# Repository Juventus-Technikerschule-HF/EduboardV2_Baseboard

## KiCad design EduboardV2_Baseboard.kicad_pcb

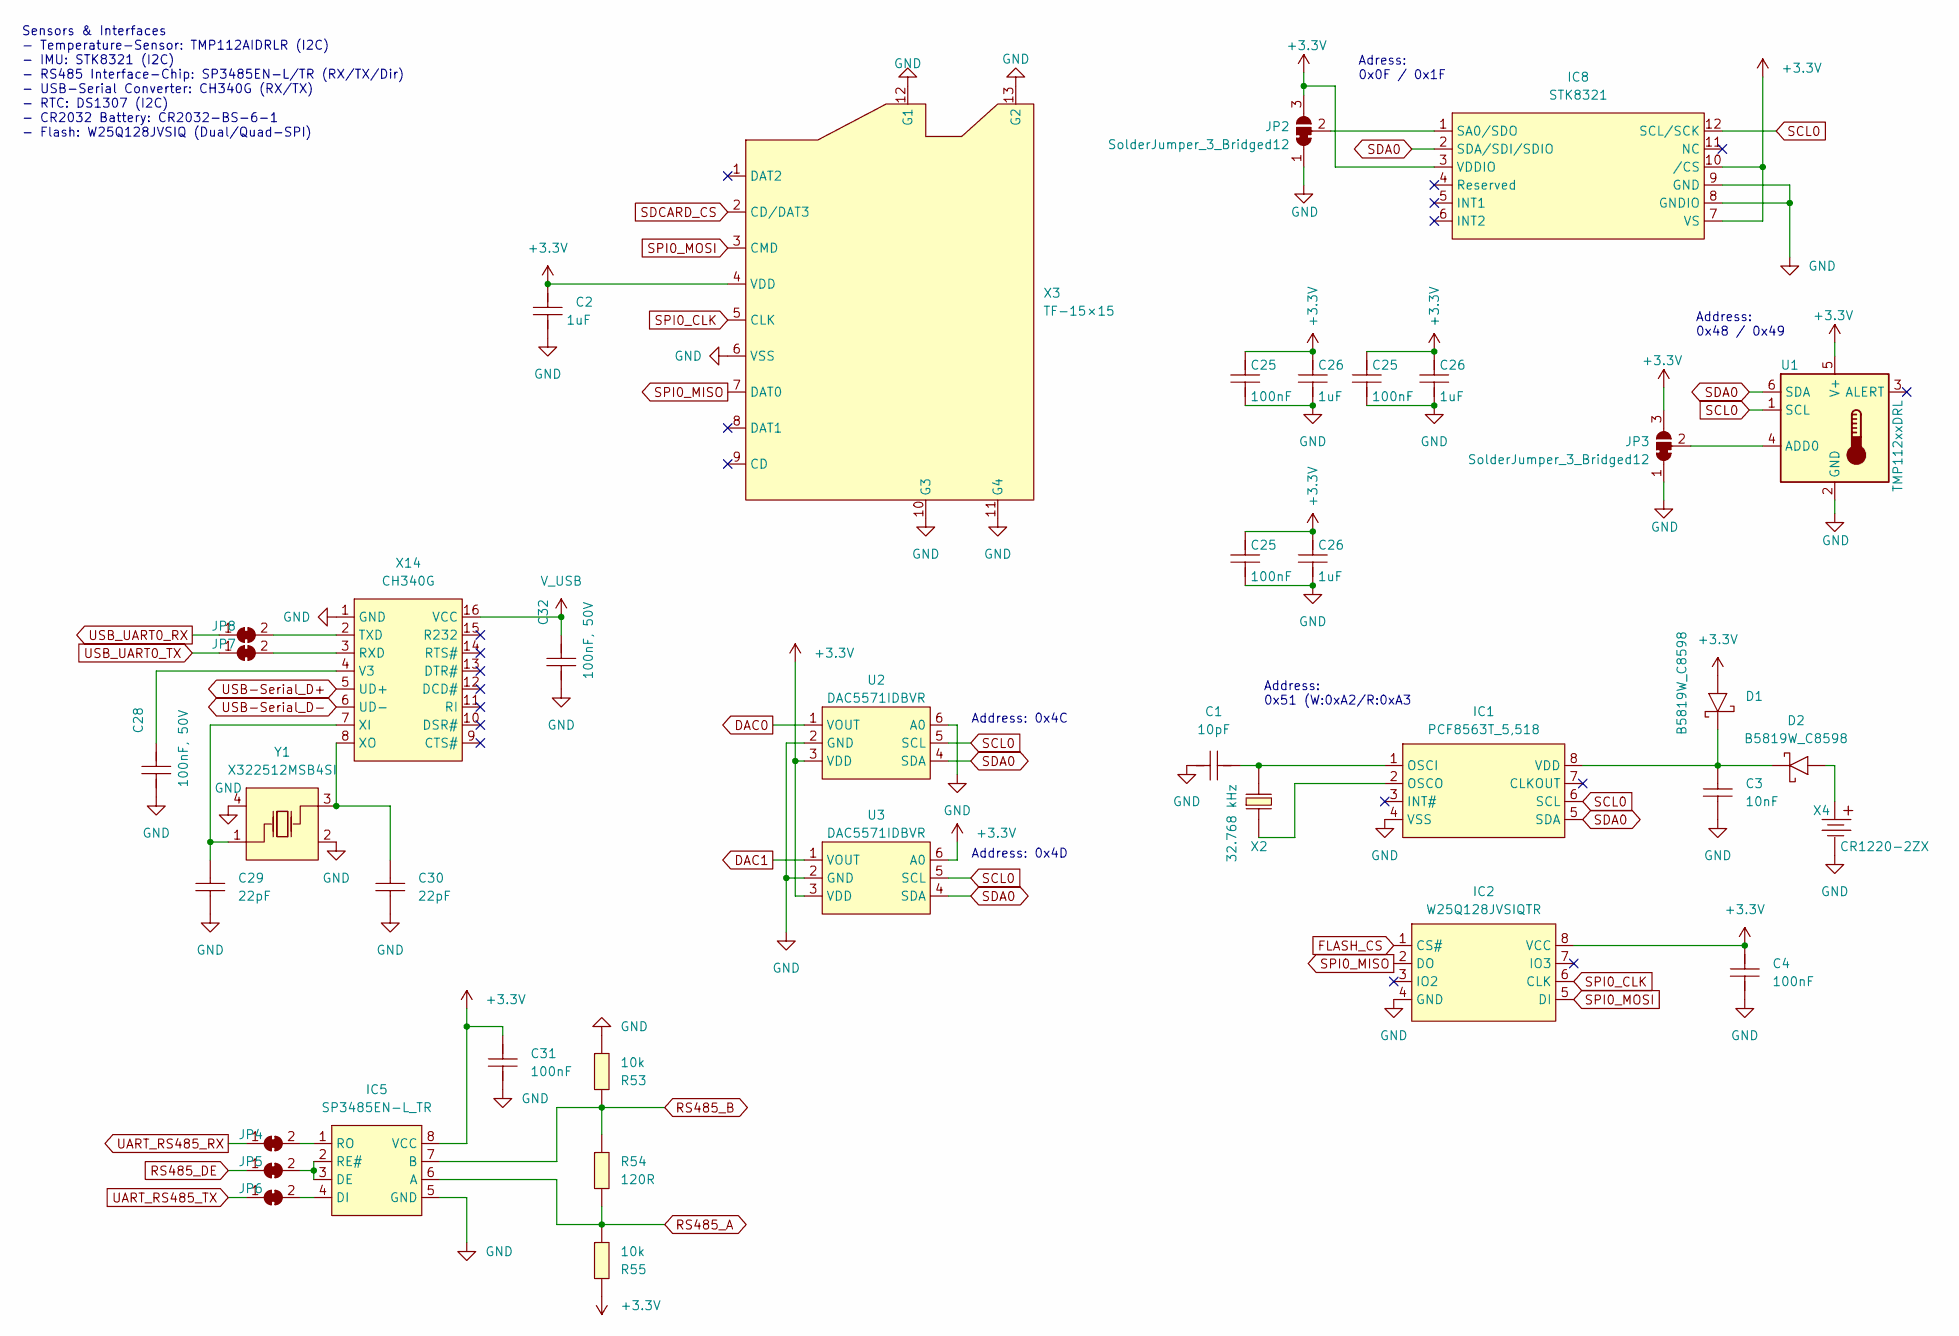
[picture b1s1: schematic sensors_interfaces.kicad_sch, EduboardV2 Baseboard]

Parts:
C1: 10pF; C_0402_1005Metric_Pad0.74x0.62mm_HandSolder; MPN CL05C100JB5NNNC; LCSC Part C32949
C2, C26: 1uF; C_0402_1005Metric_Pad0.74x0.62mm_HandSolder; MPN CL05A105KA5NQNC; LCSC Part C52923
C3: 10nF; C_0402_1005Metric_Pad0.74x0.62mm_HandSolder; MPN CL05B103KB5NNNC; LCSC Part C15195
C4, C25, C31: 100nF; C_0402_1005Metric_Pad0.74x0.62mm_HandSolder; MPN CL05B104KB54PNC; LCSC Part C307331
C28, C32: 100nF, 50V; C_0402_1005Metric_Pad0.74x0.62mm_HandSolder; MPN CL05B104KB54PNC; LCSC Part C307331
C29, C30: 22pF; C_0402_1005Metric_Pad0.74x0.62mm_HandSolder; MPN 0402CG220J500NT; LCSC Part C1555
D1, D2: B5819W_C8598; SOD-123_L2.7-W1.6-LS3.7-RD-1; MPN B5819W_C8598; LCSC Part C8598
IC1: PCF8563T_5,518; SOIC-8_L5.0-W4.0-P1.27-LS6.0-BL; MPN PCF8563T/5,518; LCSC Part C7440
IC2: W25Q128JVSIQTR; SOIC-8_L5.3-W5.3-P1.27-LS8.0-BL; MPN W25Q128JVSIQTR; LCSC Part C97521
IC5: SP3485EN-L_TR; SOIC-8_L5.0-W4.0-P1.27-LS6.0-BL; MPN SP3485EN-L/TR; LCSC Part C8963
IC8: STK8321; LGA-12_L2.0-W2.0-P0.50-TR; MPN STK8321; LCSC Part C966924
JP2, JP3: SolderJumper_3_Bridged12; SolderJumper-3_P1.3mm_Bridged12_Pad1.0x1.5mm
JP4, JP5, JP6, JP7, JP8: SolderJumper_2_Bridged; SolderJumper-2_P1.3mm_Bridged_Pad1.0x1.5mm
R53, R55: 10k; R_0402_1005Metric_Pad0.72x0.64mm_HandSolder; MPN 0402WGF1002TCE; LCSC Part C25744
R54: 120R; R_0402_1005Metric_Pad0.72x0.64mm_HandSolder; MPN 0402WGF1200TCE; LCSC Part C25079
U1: TMP112xxDRL; SOT-563; LCSC Part C28927
U2, U3: DAC5571IDBVR; SOT-23-6_L2.9-W1.6-P0.95-LS2.8-BR; LCSC Part C24061
X2: 32.768 kHz; FC-135R_L3.2-W1.5; MPN Q13FC1350000400; LCSC Part C32346
X3: TF-15×15; TF-SMD_TF-15-15; MPN TF-15×15; LCSC Part C111196
X4: CR1220-2ZX; BAT-SMD_CR1220-2ZX; MPN CR1220-2ZX; LCSC Part C969906
X14: CH340G; SOIC-16_L9.9-W3.9-P1.27-LS6.0-BL; MPN CH340G; LCSC Part C14267
Y1: X322512MSB4SI; OSC-SMD_4P-L3.2-W2.5-BL; MPN X322512MSB4SI; LCSC Part C9002

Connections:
FLASH_CS: IC2.1 (CS#); also elsewhere on the board
unnamed: C3.2, D1.1 (-), D2.1 (-), IC1.8 (VDD)
unnamed: IC5.2 (RE#), IC5.3 (DE), JP5.2 (B)
unnamed: IC5.4 (DI), JP6.2 (B)
unnamed: IC5.1 (RO), JP4.2 (B)
unnamed: IC8.1 (SA0/SDO), JP2.2 (C)
unnamed: JP3.2 (C), U1.4 (ADD0)
unnamed: JP7.2 (B), X14.3 (RXD)
unnamed: JP8.2 (B), X14.2 (TXD)
unnamed: C28.2, X14.4 (V3)
unnamed: C29.2, X14.7 (XI), Y1.1 (OSC1)
unnamed: C30.2, X14.8 (XO), Y1.3 (OSC2)
RS485_A: IC5.6 (A), R54.1, R55.1; also elsewhere on the board
RS485_B: IC5.7 (B), R53.2, R54.2; also elsewhere on the board
RS485_DE: JP5.1 (A); also elsewhere on the board
SCL0: IC1.6 (SCL), IC8.12 (SCL/SCK), U1.1 (SCL), U2.5 (SCL), U3.5 (SCL); also elsewhere on the board
SDA0: IC1.5 (SDA), IC8.2 (SDA/SDI/SDIO), U1.6 (SDA), U2.4 (SDA), U3.4 (SDA); also elsewhere on the board
SDCARD_CS: X3.2 (CD/DAT3); also elsewhere on the board
SPI0_MISO: IC2.2 (DO), X3.7 (DAT0); also elsewhere on the board
SPI0_MOSI: IC2.5 (DI), X3.3 (CMD); also elsewhere on the board
UART_RS485_RX: JP4.1 (A); also elsewhere on the board
UART_RS485_TX: JP6.1 (A); also elsewhere on the board
USB-Serial_D+: X14.5 (UD+); also elsewhere on the board
USB-Serial_D-: X14.6 (UD-); also elsewhere on the board
USB_UART0_TX: JP7.1 (A); also elsewhere on the board
V_USB: C32.2, X14.16 (VCC); also elsewhere on the board

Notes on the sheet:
Sensors & Interfaces - Temperature-Sensor: TMP112AIDRLR (I2C) - IMU: STK8321 (I2C) - RS485 Interface-Chip: SP3485EN-L/TR (RX/TX/Dir) - USB-Serial Converter: CH340G (RX/TX) - RTC: DS1307 (I2C) - CR2032 Battery: CR2032-BS-6-1 - Flash: W25Q128JVSIQ (Dual/Quad-SPI)
Adress: 0x0F / 0x1F
Address: 0x51 (W:0xA2/R:0xA3
Address: 0x4C
Address: 0x48 / 0x49
Address: 0x4D

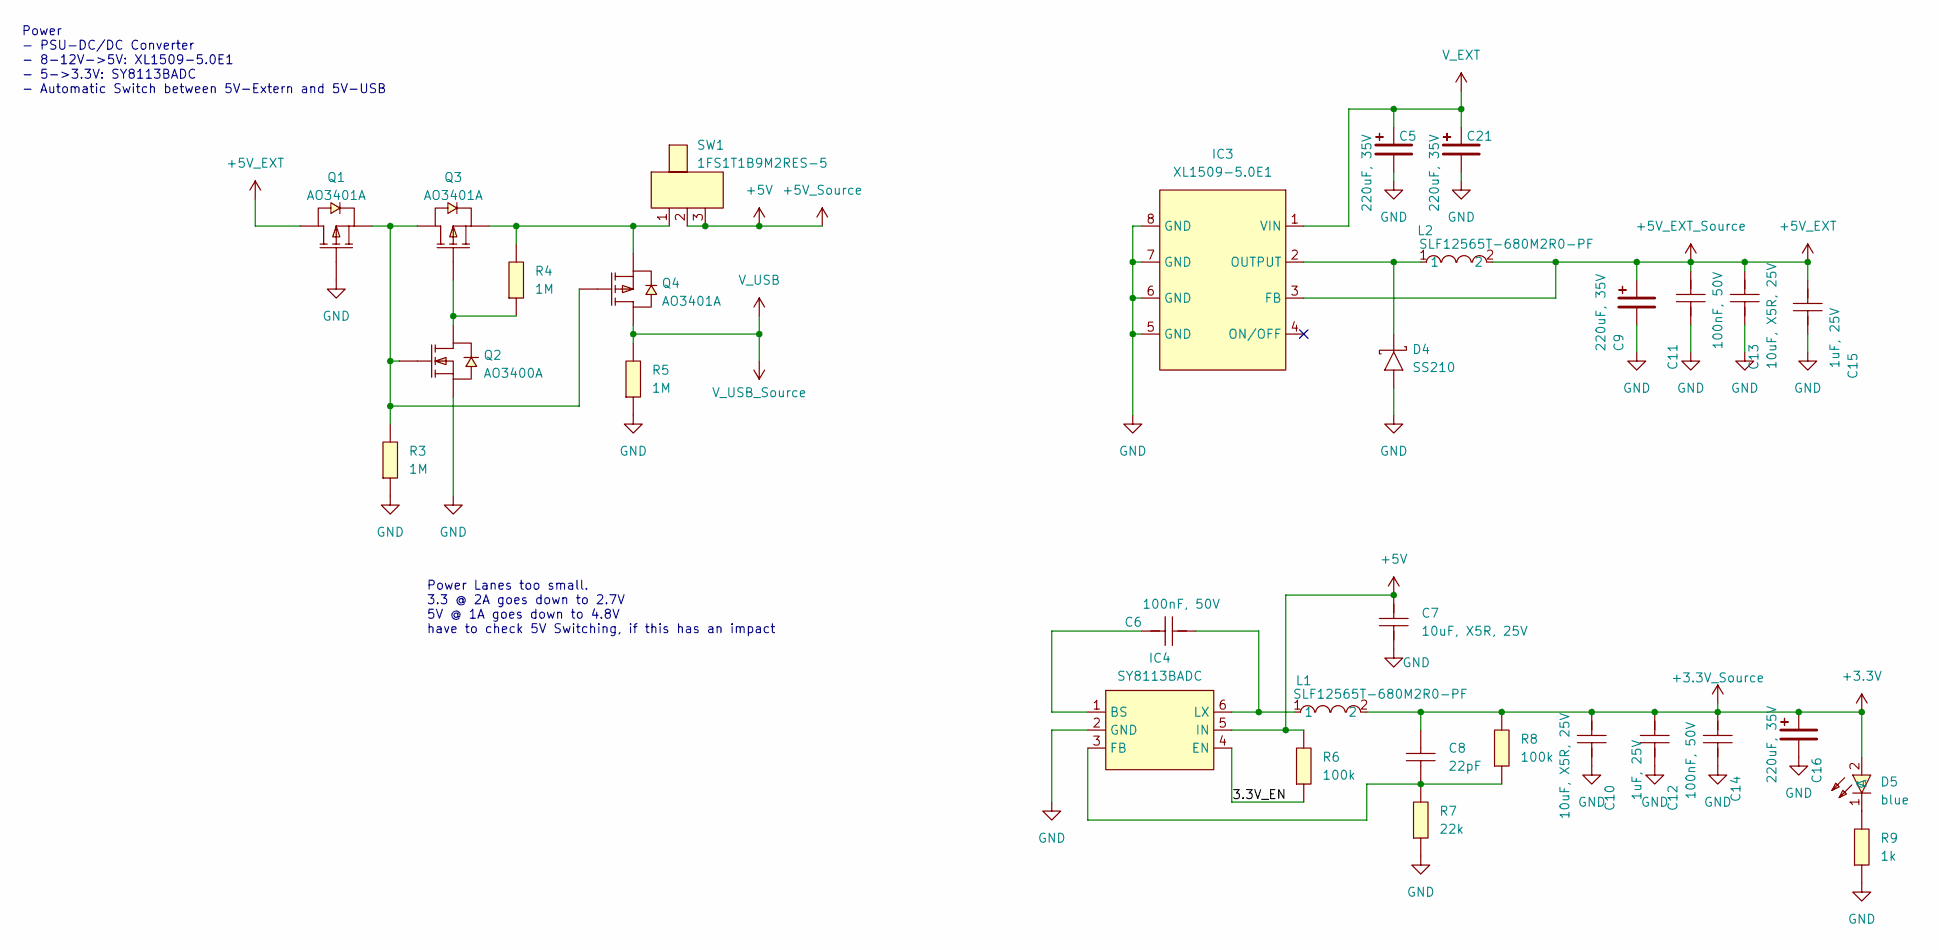
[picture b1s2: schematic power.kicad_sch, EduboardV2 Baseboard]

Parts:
C5, C9, C16, C21: 220uF, 35V; CAP-SMD_BD8.0-L8.3-W8.3-RD; MPN VEJ221M1VTR-0810; LCSC Part C164065
C6, C11, C14: 100nF, 50V; C_0402_1005Metric_Pad0.74x0.62mm_HandSolder; MPN CL05B104KB54PNC; LCSC Part C307331
C7, C10, C13: 10uF, X5R, 25V; C_0603_1608Metric_Pad1.08x0.95mm_HandSolder; MPN CL10A106MA8NRNC; LCSC Part C96446
C8: 22pF; C_0402_1005Metric_Pad0.74x0.62mm_HandSolder; MPN 0402CG220J500NT; LCSC Part C1555
C12, C15: 1uF, 25V; C_0402_1005Metric_Pad0.74x0.62mm_HandSolder; MPN CL05A105KA5NQNC; LCSC Part C52923
D4: SS210; SMA_L4.3-W2.6-LS5.2-RD; MPN SS210; LCSC Part C14996
D5: blue; LED0603-FD_BLUE; MPN 19-217/BHC-ZL1M2RY/3T; LCSC Part C72041
IC3: XL1509-5.0E1; SOIC-8_L5.0-W4.0-P1.27-LS6.0-BL; MPN XL1509-5.0E1; LCSC Part C61063
IC4: SY8113BADC; TSOT-23-6_L2.9-W1.6-P0.95-LS2.8-BR; MPN SY8113BADC; LCSC Part C78989
L1, L2: SLF12565T-680M2R0-PF; IND-SMD_L12.5-W12.5_SLF12565T; LCSC Part C136216
Q1, Q3, Q4: AO3401A; SOT-23_L2.9-W1.3-P1.90-LS2.4-BR; MPN AO3401A; LCSC Part C15127
Q2: AO3400A; SOT-23-3_L2.9-W1.6-P1.90-LS2.8-BR; MPN AO3400A; LCSC Part C20917
R3, R4, R5: 1M; R_0402_1005Metric_Pad0.72x0.64mm_HandSolder; MPN 0402WGF1003TCE; LCSC Part C25741
R6, R8: 100k; R_0402_1005Metric_Pad0.72x0.64mm_HandSolder; MPN 0402WGF1003TCE; LCSC Part C25741
R7: 22k; R_0402_1005Metric_Pad0.72x0.64mm_HandSolder; MPN 0402WGF2202TCE; LCSC Part C25768
R9: 1k; R_0402_1005Metric_Pad0.72x0.64mm_HandSolder; MPN 0402WGF1001TCE; LCSC Part C11702
SW1: 1FS1T1B9M2RES-5; SW-TH_1FS1T1B9M2RES-5; MPN 1FS1T1B9M2RES-5; LCSC Part C496164

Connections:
+5V: C7.2, IC4.5 (IN), R6.2, SW1.2, SW1.3; also elsewhere on the board
+5V_EXT: C9.1, C11.1, C13.2, C15.1, IC3.3 (FB), L2.2, Q1.3 (D)
/Power/3.3V_EN: IC4.4 (EN), R6.1
unnamed: D4.1 (K), IC3.2 (OUTPUT), L2.1
unnamed: D5.1 (C), R9.2
unnamed: C6.1, IC4.1 (BS)
unnamed: C8.1, IC4.3 (FB), R7.2, R8.1
unnamed: C6.2, IC4.6 (LX), L1.1
unnamed: Q1.2 (S), Q2.1 (G), Q3.3 (D), Q4.1 (G), R3.2
unnamed: Q2.3 (D), Q3.1 (G), R4.1
unnamed: Q3.2 (S), Q4.2 (S), R4.2, SW1.1
V_USB: Q4.3 (D), R5.2; also elsewhere on the board

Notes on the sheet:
Power Lanes too small. 3.3 @ 2A goes down to 2.7V 5V @ 1A goes down to 4.8V have to check 5V Switching, if this has an impact
Power - PSU-DC/DC Converter - 8-12V->5V: XL1509-5.0E1 - 5->3.3V: SY8113BADC - Automatic Switch between 5V-Extern and 5V-USB

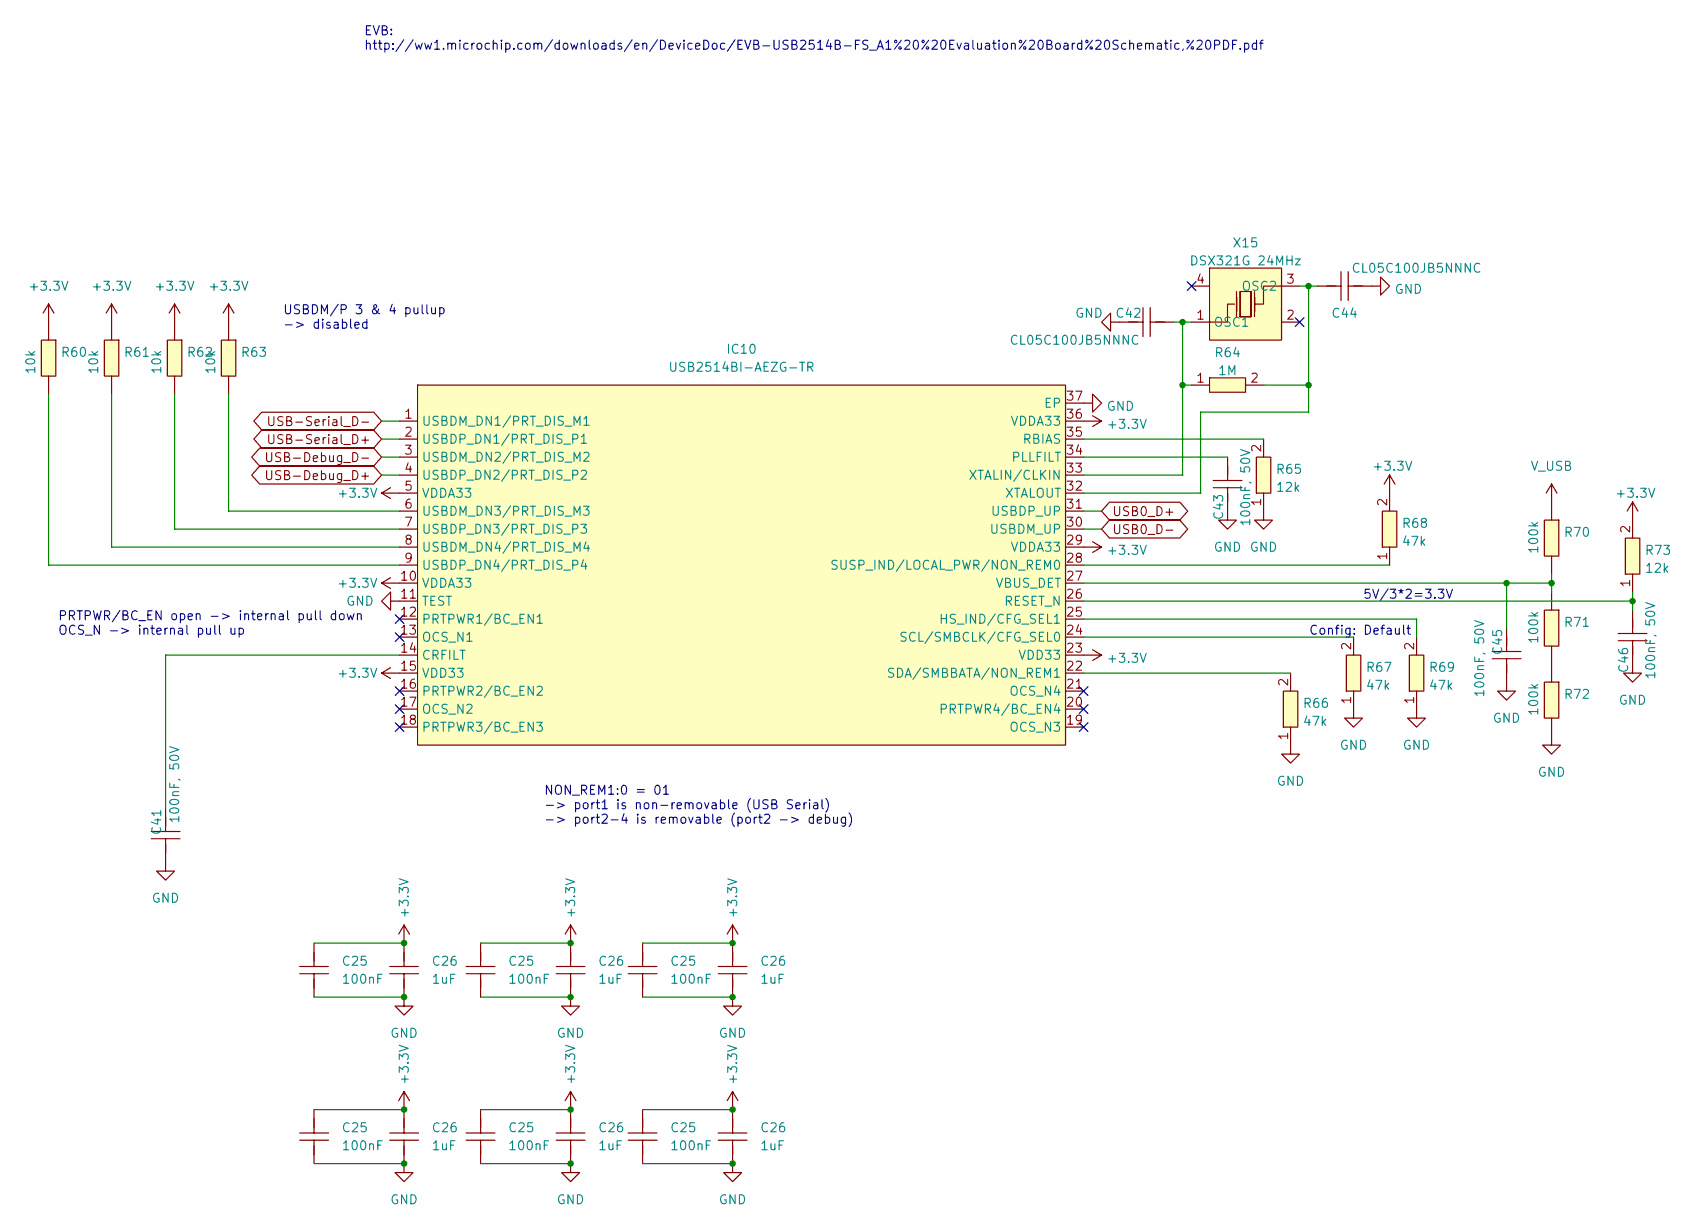
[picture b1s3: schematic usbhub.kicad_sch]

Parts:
C25: 100nF; C_0402_1005Metric_Pad0.74x0.62mm_HandSolder; MPN CL05B104KB54PNC; LCSC Part C307331
C26: 1uF; C_0402_1005Metric_Pad0.74x0.62mm_HandSolder; MPN CL05A105KA5NQNC; LCSC Part C52923
C41, C43, C45, C46: 100nF, 50V; C_0402_1005Metric_Pad0.74x0.62mm_HandSolder; MPN CL05B104KB54PNC; LCSC Part C307331
C42, C44: CL05C100JB5NNNC; C_0402_1005Metric_Pad0.74x0.62mm_HandSolder; MPN CL05C100JB5NNNC; LCSC Part C32949
IC10: USB2514BI-AEZG-TR; TQFN-36_L6.0-W6.0-P0.50-BL-EP3.7; MPN USB2514BI-AEZG-TR; LCSC Part C58940
R60, R61, R62, R63: 10k; R_0402_1005Metric_Pad0.72x0.64mm_HandSolder; MPN 0402WGF1002TCE; LCSC Part C25744
R64: 1M; R_0402_1005Metric_Pad0.72x0.64mm_HandSolder; LCSC Part C25741
R65, R73: 12k; R_0402_1005Metric_Pad0.72x0.64mm_HandSolder; LCSC Part C25752
R66, R67, R68, R69: 47k; R_0402_1005Metric_Pad0.72x0.64mm_HandSolder; LCSC Part C25792
R70, R71, R72: 100k; R_0402_1005Metric_Pad0.72x0.64mm_HandSolder; MPN 0402WGF1003TCE; LCSC Part C25741
X15: DSX321G 24MHz; OSC-SMD_4P-L3.2-W2.5-BL; LCSC Part C93235

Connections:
unnamed: C41.1, IC10.14 (CRFILT)
unnamed: IC10.25 (HS_IND/CFG_SEL1), R69.2
unnamed: C43.1, IC10.34 (PLLFILT)
unnamed: IC10.35 (RBIAS), R65.2
unnamed: C46.1, IC10.26 (RESET_N), R73.1
unnamed: IC10.24 (SCL/SMBCLK/CFG_SEL0), R67.2
unnamed: IC10.22 (SDA/SMBBATA/NON_REM1), R66.2
unnamed: IC10.28 (SUSP_IND/LOCAL_PWR/NON_REM0), R68.1
unnamed: IC10.6 (USBDM_DN3/PRT_DIS_M3), R63.2
unnamed: IC10.8 (USBDM_DN4/PRT_DIS_M4), R61.2
unnamed: IC10.7 (USBDP_DN3/PRT_DIS_P3), R62.2
unnamed: IC10.9 (USBDP_DN4/PRT_DIS_P4), R60.2
unnamed: C45.1, IC10.27 (VBUS_DET), R70.2, R71.1
unnamed: C42.2, IC10.33 (XTALIN/CLKIN), R64.1, X15.1 (OSC1)
unnamed: C44.1, IC10.32 (XTALOUT), R64.2, X15.3 (OSC2)
unnamed: R71.2, R72.1
USB0_D+: IC10.31 (USBDP_UP); also elsewhere on the board
USB0_D-: IC10.30 (USBDM_UP); also elsewhere on the board
USB-Debug_D+: IC10.4 (USBDP_DN2/PRT_DIS_P2); also elsewhere on the board
USB-Debug_D-: IC10.3 (USBDM_DN2/PRT_DIS_M2); also elsewhere on the board
USB-Serial_D+: IC10.2 (USBDP_DN1/PRT_DIS_P1); also elsewhere on the board
USB-Serial_D-: IC10.1 (USBDM_DN1/PRT_DIS_M1); also elsewhere on the board
V_USB: R70.1; also elsewhere on the board

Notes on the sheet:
PRTPWR/BC_EN open -> internal pull down OCS_N -> internal pull up
EVB: http://ww1.microchip.com/downloads/en/DeviceDoc/EVB-USB2514B-FS_A1%20%20Evaluation%20Board%20Schematic,%20PDF.pdf
5V/3*2=3.3V
Config: Default
USBDM/P 3 & 4 pullup -> disabled
NON_REM1:0 = 01 -> port1 is non-removable (USB Serial) -> port2-4 is removable (port2 -> debug)

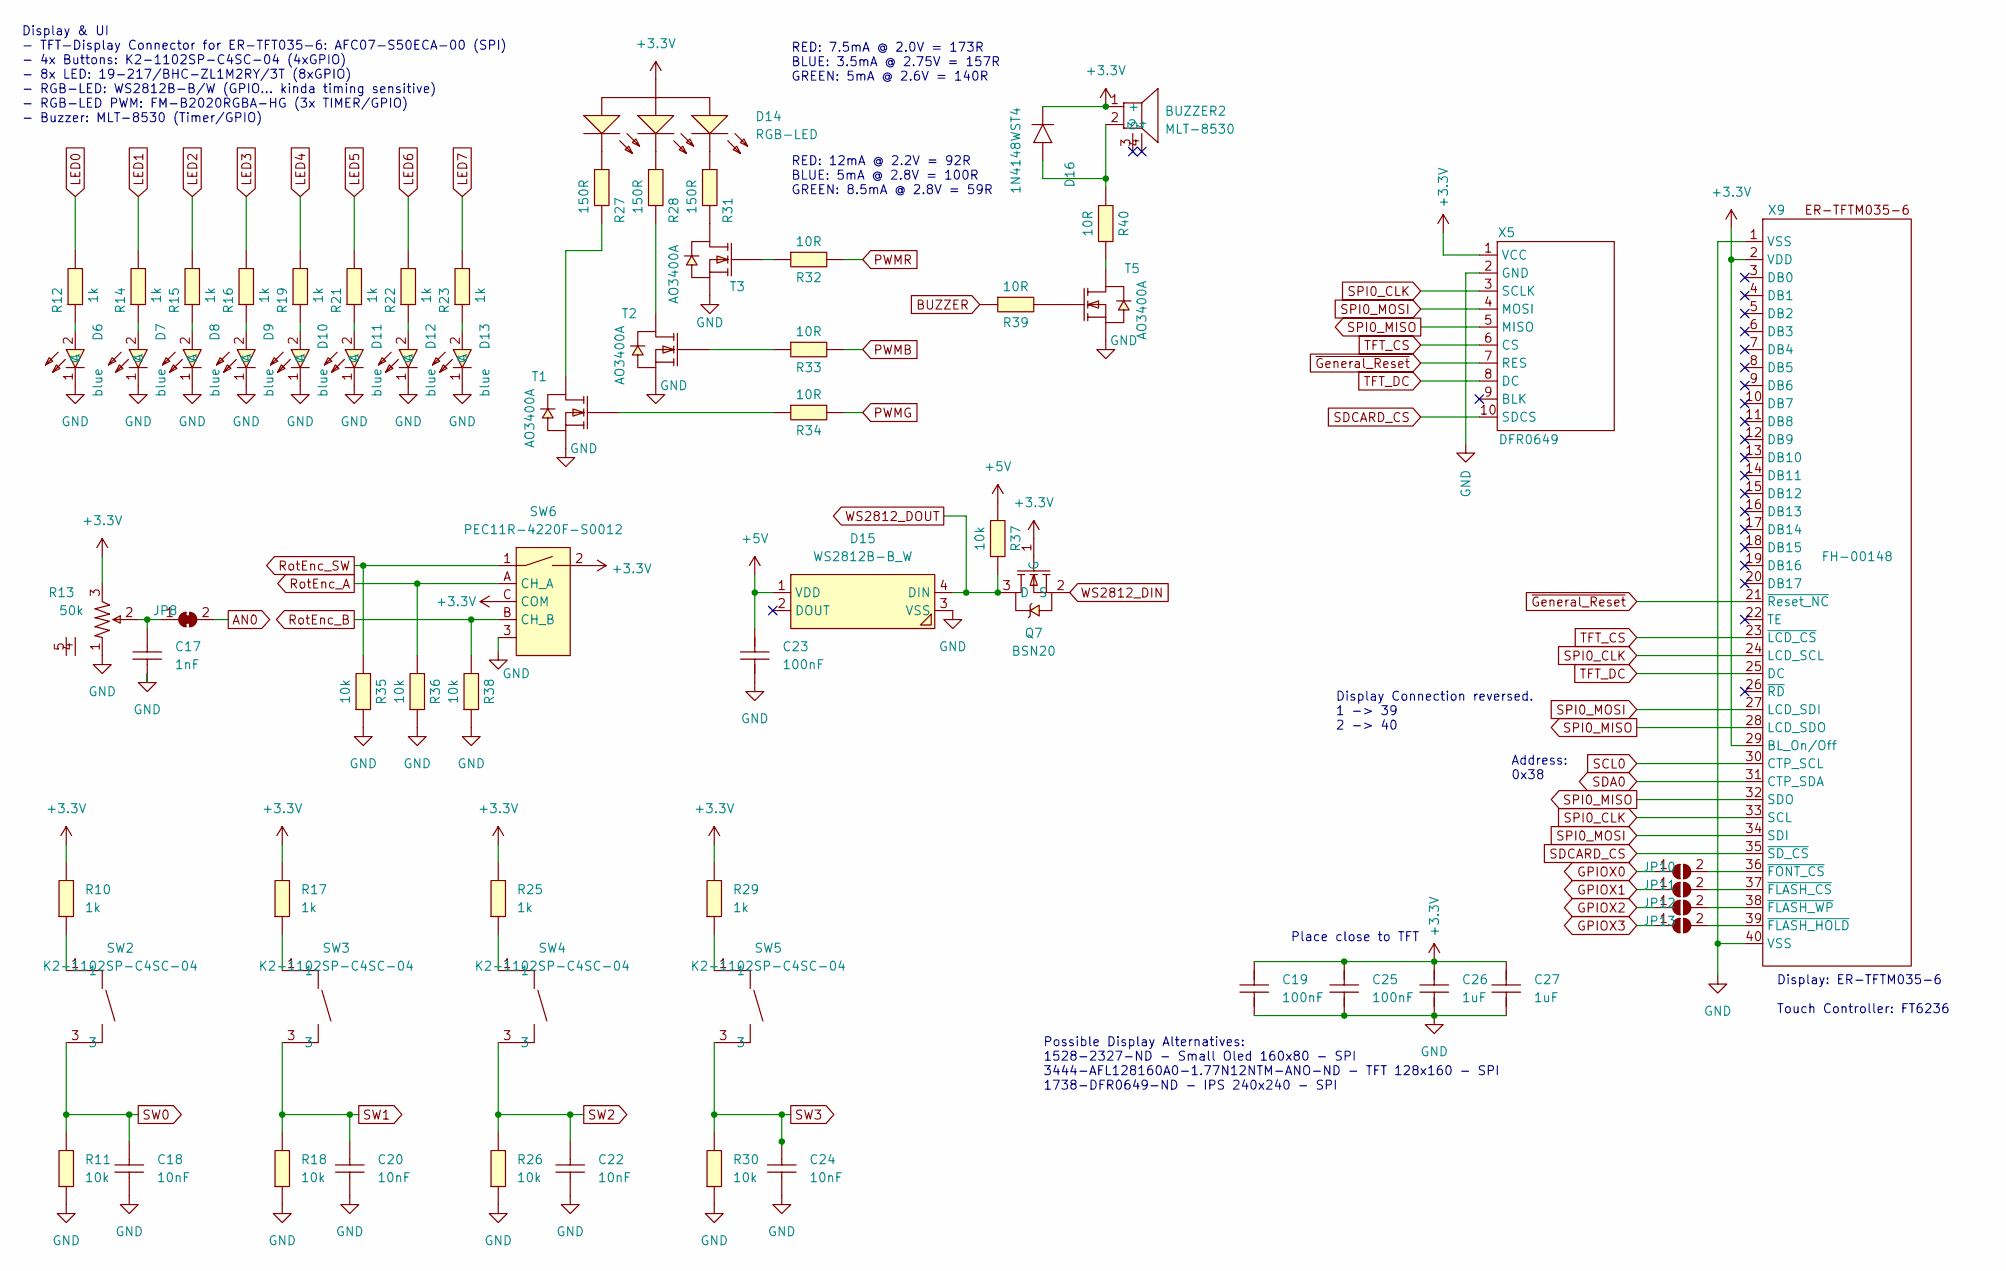
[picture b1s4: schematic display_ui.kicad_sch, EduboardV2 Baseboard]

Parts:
BUZZER2: MLT-8530; BUZ-SMD_4P-L8.5-W8.5-P8.50-BR; LCSC Part C94599
C17: 1nF; C_0402_1005Metric_Pad0.74x0.62mm_HandSolder; MPN 0402B102K500NT; LCSC Part C1523
C18, C20, C22, C24: 10nF; C_0402_1005Metric_Pad0.74x0.62mm_HandSolder; MPN CL05B103KB5NNNC; LCSC Part C15195
C19, C23, C25: 100nF; C_0402_1005Metric_Pad0.74x0.62mm_HandSolder; MPN CL05B104KB54PNC; LCSC Part C307331
C26, C27: 1uF; C_0402_1005Metric_Pad0.74x0.62mm_HandSolder; MPN CL05A105KA5NQNC; LCSC Part C52923
D6, D7, D8, D9, D10, D11, D12, D13: blue; LED0603-FD_BLUE; MPN 19-217/BHC-ZL1M2RY/3T; LCSC Part C72041
D14: RGB-LED; LED-SMD_FM-B2020RGBA-HG; MPN FM-B2020RGBA-HG; LCSC Part C108793
D15: WS2812B-B_W; LED-SMD_4P-L5.0-W5.0-TL_WS2812B-B; MPN WS2812B-B/W; LCSC Part C2761795
D16: 1N4148WST4; SOD-323_L1.8-W1.3-LS2.5-RD; MPN 1N4148WS T4; LCSC Part C2128
JP8: SolderJumper_2_Bridged; SolderJumper-2_P1.3mm_Bridged_Pad1.0x1.5mm
JP10, JP11, JP12, JP13: SolderJumper_2_Open; SolderJumper-2_P1.3mm_Open_Pad1.0x1.5mm
Q7: BSN20; SOT-23-3_L2.9-W1.6-P1.90-LS2.8-BR; LCSC Part C116157
R10, R12, R14, R15, R16, R17, R19, R21, R22, R23, R25, R29: 1k; R_0402_1005Metric_Pad0.72x0.64mm_HandSolder; MPN 0402WGF1001TCE; LCSC Part C11702
R11, R18, R26, R30: 10k; R_0402_1005Metric_Pad0.72x0.64mm_HandSolder; MPN 0402WGF1002TCE; LCSC Part C25744
R13: 50k; RES-TH_RK09K1130AAU; MPN RK09K1130ACL; LCSC Part C470291
R27, R28, R31: 150R; R_0402_1005Metric_Pad0.72x0.64mm_HandSolder; MPN 0402WGF1500TCE; LCSC Part C25082
R32, R33, R34, R39, R40: 10R; R_0402_1005Metric_Pad0.72x0.64mm_HandSolder; MPN 0402WGF100JTCE; LCSC Part C25077
R35, R36, R37, R38: 10k; R_0402_1005Metric_Pad0.72x0.64mm_HandSolder; MPN 0402WGF100JTCE; LCSC Part C25744
SW2, SW3, SW4, SW5: K2-1102SP-C4SC-04; KEY-SMD_4P-L6.0-W6.0-P4.50-LS9.5-BL; LCSC Part C127509
SW6: PEC11R-4220F-S0012; SW-TH_PEC11R-4220F-S0012; MPN PEC11R-4220F-S0012; LCSC Part C143817
T1, T2, T3, T5: AO3400A; SOT-23-3_L2.9-W1.6-P1.90-LS2.8-BR; MPN AO3400A; LCSC Part C20917
X5: DFR0649; Digikey 1738-DFR0649-ND
X9: FH-00148; HDR-SMD_40P-P2.54-V-F-R2-C20-S7.1-EH; MPN FH-00148; LCSC Part C2685092

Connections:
+5V: C23.2, D15.1 (VDD), R37.2; also elsewhere on the board
BUZZER: R39.1; also elsewhere on the board
GPIOX0: JP10.1 (A); also elsewhere on the board
GPIOX1: JP11.1 (A); also elsewhere on the board
GPIOX2: JP12.1 (A); also elsewhere on the board
GPIOX3: JP13.1 (A); also elsewhere on the board
LED0: R12.2; also elsewhere on the board
LED1: R14.2; also elsewhere on the board
LED2: R15.2; also elsewhere on the board
LED3: R16.2; also elsewhere on the board
LED4: R19.2; also elsewhere on the board
LED5: R21.2; also elsewhere on the board
LED6: R22.2; also elsewhere on the board
LED7: R23.2; also elsewhere on the board
unnamed: D6.2 (A), R12.1
unnamed: D7.2 (A), R14.1
unnamed: D8.2 (A), R15.1
unnamed: D9.2 (A), R16.1
unnamed: D10.2 (A), R19.1
unnamed: D11.2 (A), R21.1
unnamed: D12.2 (A), R22.1
unnamed: D13.2 (A), R23.1
unnamed: D14.1 (K), R31.2
unnamed: D14.2 (K), R28.2
unnamed: D14.4 (K), R27.2
unnamed: BUZZER2.2, D16.2 (A), R40.2
unnamed 59: JP8.2 (B); also elsewhere on the board
unnamed: JP10.2 (B), X9.36 (~FONT_CS)
unnamed: JP11.2 (B), X9.37 (~FLASH_CS)
unnamed: JP12.2 (B), X9.38 (~FLASH_WP)
unnamed: JP13.2 (B), X9.39 (~FLASH_HOLD)
unnamed: R10.1, SW2.1, SW2.2
unnamed: R17.1, SW3.1, SW3.2
unnamed: R25.1, SW4.1, SW4.2
unnamed: R29.1, SW5.1, SW5.2
unnamed: R27.1, T1.3 (D)
unnamed: R34.1, T1.1 (G)
unnamed: R28.1, T2.3 (D)
unnamed: R33.1, T2.1 (G)
unnamed: R31.1, T3.3 (D)
unnamed: R32.1, T3.1 (G)
unnamed: R40.1, T5.3 (D)
unnamed: R39.2, T5.1 (G)
PWMB: R33.2; also elsewhere on the board
PWMG: R34.2; also elsewhere on the board
PWMR: R32.2; also elsewhere on the board
RotEnc_A: R36.2, SW6.A (CH_A); also elsewhere on the board
RotEnc_B: R38.2, SW6.B (CH_B); also elsewhere on the board
RotEnc_SW: R35.2, SW6.1; also elsewhere on the board
SCL0: X9.30 (CTP_SCL); also elsewhere on the board
SDA0: X9.31 (CTP_SDA); also elsewhere on the board
SDCARD_CS: X5.10 (SDCS), X9.35 (~SD_CS); also elsewhere on the board
SPI0_MISO: X5.5 (MISO), X9.28 (LCD_SDO), X9.32 (SDO); also elsewhere on the board
SPI0_MOSI: X5.4 (MOSI), X9.27 (LCD_SDI), X9.34 (SDI); also elsewhere on the board
SW0: C18.2, R11.2, SW2.3, SW2.4; also elsewhere on the board
SW1: C20.2, R18.2, SW3.3, SW3.4; also elsewhere on the board
SW2: C22.2, R26.2, SW4.3, SW4.4; also elsewhere on the board
SW3: C24.2, R30.2, SW5.3, SW5.4; also elsewhere on the board
TFT_CS: X5.6 (CS), X9.23 (~LCD_CS); also elsewhere on the board
TFT_DC: X5.8 (DC), X9.25 (DC); also elsewhere on the board
WS2812_DOUT: D15.4 (DIN), Q7.3 (D), R37.1; also elsewhere on the board
~General_Reset: X5.7 (RES), X9.21 (~Reset_NC); also elsewhere on the board

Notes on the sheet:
Display & UI - TFT-Display Connector for ER-TFT035-6: AFC07-S50ECA-00 (SPI) - 4x Buttons: K2-1102SP-C4SC-04 (4xGPIO) - 8x LED: 19-217/BHC-ZL1M2RY/3T (8xGPIO) - RGB-LED: WS2812B-B/W (GPIO... kinda timing sensitive) - RGB-LED PWM: FM-B2020RGBA-HG (3x TIMER/GPIO) - Buzzer: MLT-8530 (Timer/GPIO)
RED: 7.5mA @ 2.0V = 173R BLUE: 3.5mA @ 2.75V = 157R GREEN: 5mA @ 2.6V = 140R
Address: 0x38
Display: ER-TFTM035-6 Touch Controller: FT6236
Place close to TFT
RED: 12mA @ 2.2V = 92R BLUE: 5mA @ 2.8V = 100R GREEN: 8.5mA @ 2.8V = 59R
Possible Display Alternatives: 1528-2327-ND - Small Oled 160x80 - SPI 3444-AFL128160A0-1.77N12NTM-ANO-ND - TFT 128x160 - SPI 1738-DFR0649-ND - IPS 240x240 - SPI
Display Connection reversed. 1 -> 39 2 -> 40

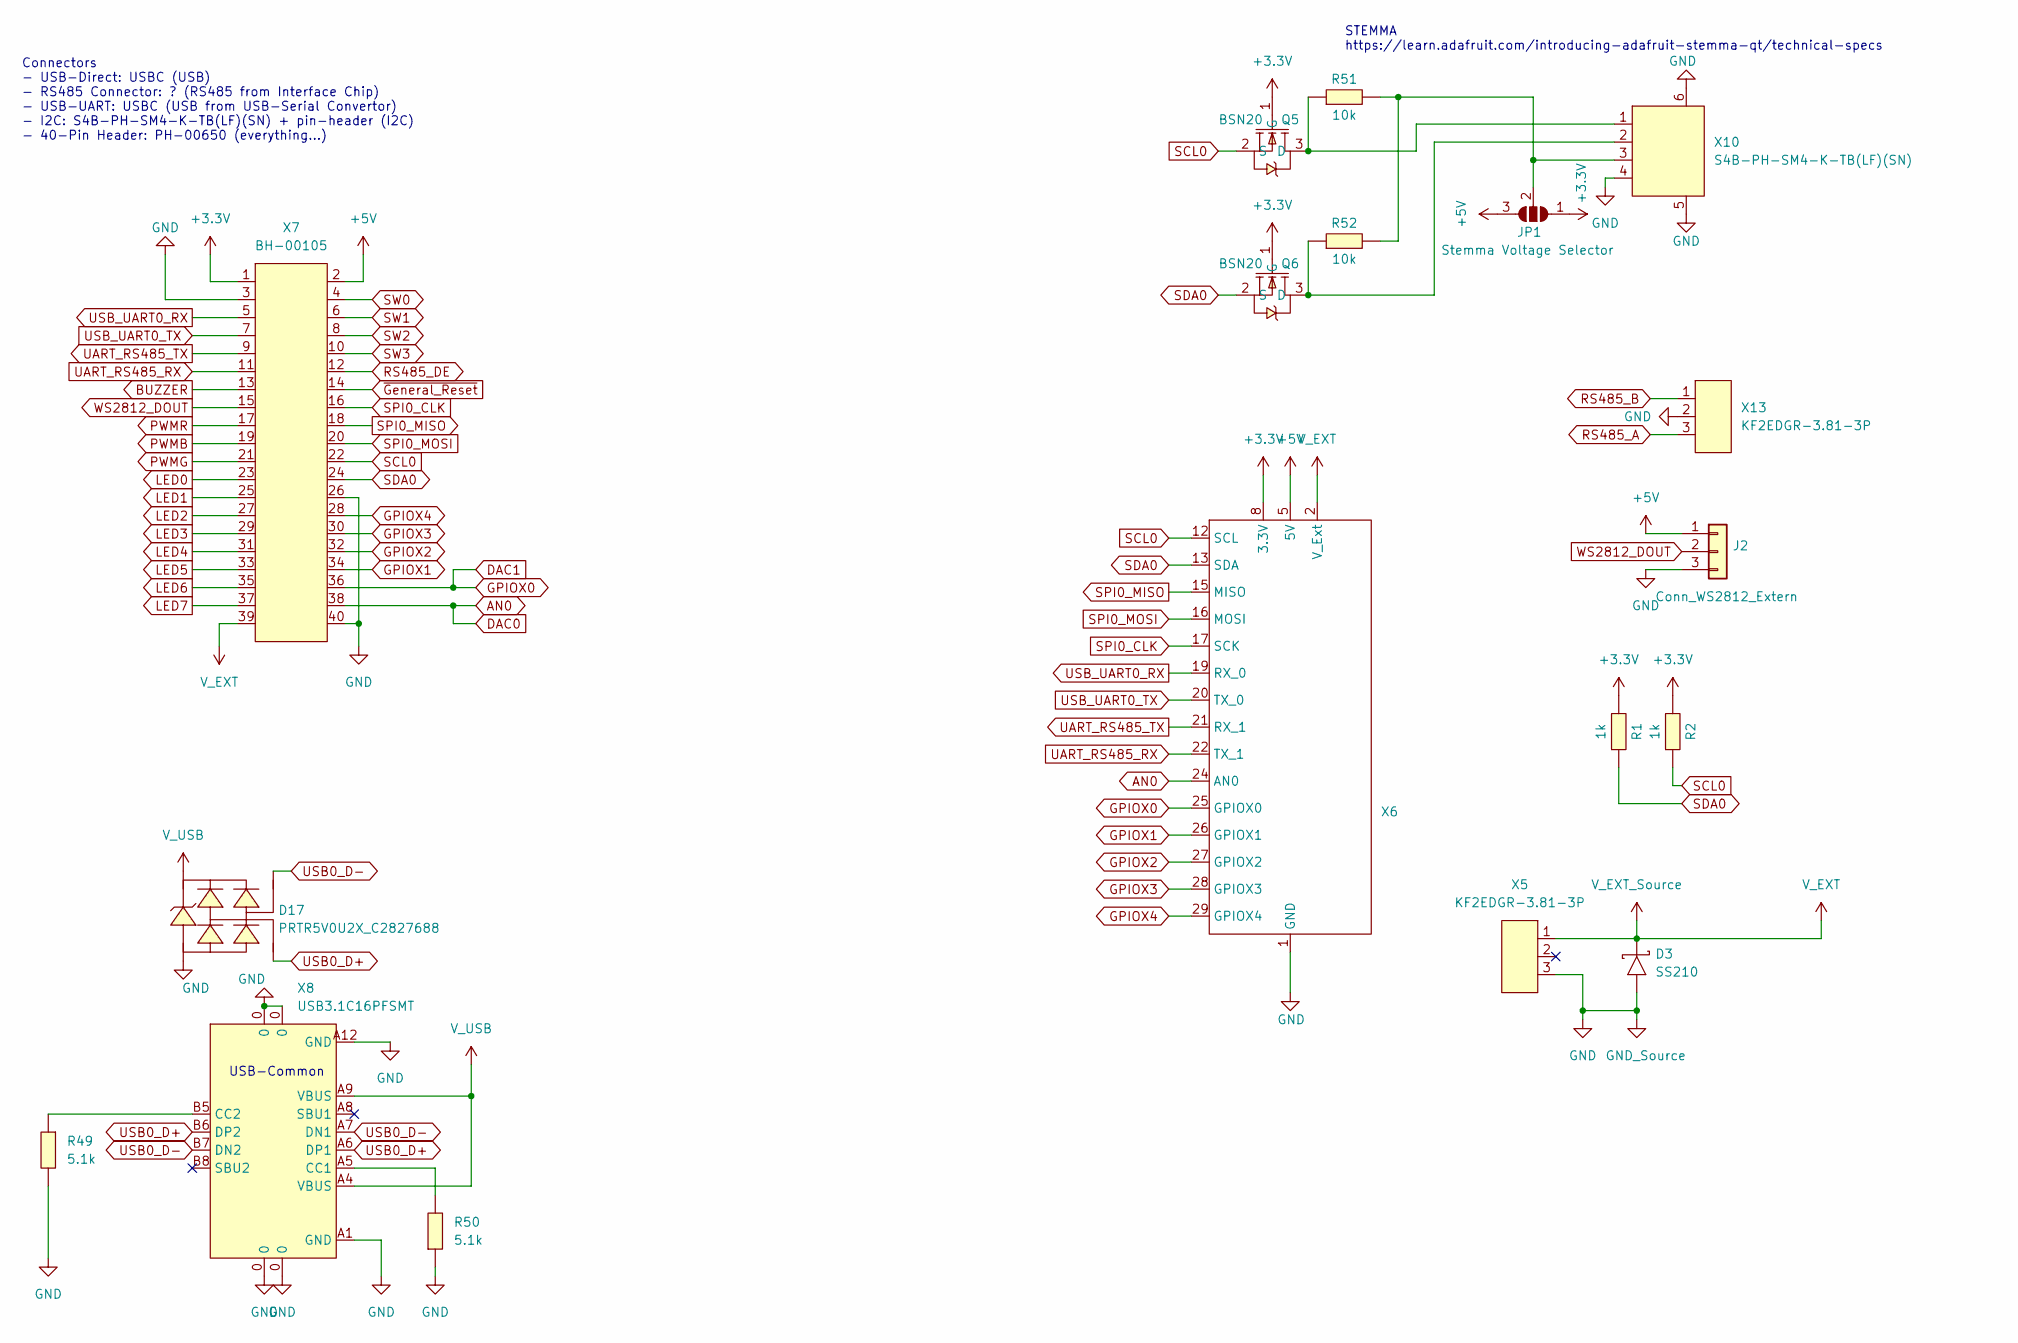
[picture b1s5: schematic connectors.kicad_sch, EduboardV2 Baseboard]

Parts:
D3: SS210; SMA_L4.3-W2.6-LS5.2-RD; MPN SS210; LCSC Part C14996
D17: PRTR5V0U2X_C2827688; SOT-143-4_L2.9-W1.3-P1.92-LS2.4-BL; LCSC Part C2827688
J2: Conn_WS2812_Extern; PinHeader_1x03_P2.54mm_Vertical
JP1: Stemma Voltage Selector; SolderJumper-3_P1.3mm_Open_RoundedPad1.0x1.5mm
Q5, Q6: BSN20; SOT-23-3_L2.9-W1.6-P1.90-LS2.8-BR; LCSC Part C116157
R1, R2: 1k; R_0402_1005Metric_Pad0.72x0.64mm_HandSolder; MPN 0402WGF100JTCE; LCSC Part C11702
R49, R50: 5.1k; R_0402_1005Metric_Pad0.72x0.64mm_HandSolder; MPN 0402WGF5101TCE; LCSC Part C25905
R51, R52: 10k; R_0402_1005Metric_Pad0.72x0.64mm_HandSolder; MPN 0402WGF100JTCE; LCSC Part C25744
X5, X13: KF2EDGR-3.81-3P; CONN-TH_3P-P3.81_KF2EDGR-3.81-3P; MPN KF2EDGR-3.81-3P; LCSC Part C441183
X6: protoboard_patch
X7: BH-00105; IDC-SMD_BH-00105; MPN BH-00105; LCSC Part C2685065
X8: USB3.1C16PFSMT; USB-C-SMD_TYPE-C-USB-17; MPN USB3.1C16PFSMT; LCSC Part C167321
X10: S4B-PH-SM4-K-TB(LF)(SN); CONN-SMD_S4B-PH-SM4-K-TB-LF-SN; MPN S4B-PH-SM4-K-TB(LF)(SN); LCSC Part C265332

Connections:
+5V: J2.1, JP1.3 (B), X6.5 (5V), X6.6 (5V), X6.35 (5V), X6.36 (5V), X7.2; also elsewhere on the board
AN0: X6.24 (AN0), X7.38; also elsewhere on the board
BUZZER: X7.13; also elsewhere on the board
GPIOX0: X6.25 (GPIOX0), X7.36; also elsewhere on the board
GPIOX1: X6.26 (GPIOX1), X7.34; also elsewhere on the board
GPIOX2: X6.27 (GPIOX2), X7.32; also elsewhere on the board
GPIOX3: X6.28 (GPIOX3), X7.30; also elsewhere on the board
GPIOX4: X6.29 (GPIOX4), X7.28; also elsewhere on the board
LED0: X7.23; also elsewhere on the board
LED1: X7.25; also elsewhere on the board
LED2: X7.27; also elsewhere on the board
LED3: X7.29; also elsewhere on the board
LED4: X7.31; also elsewhere on the board
LED5: X7.33; also elsewhere on the board
LED6: X7.35; also elsewhere on the board
LED7: X7.37; also elsewhere on the board
unnamed: JP1.2 (C), R51.2, R52.2, X10.3
unnamed 80: Q5.3 (D), R51.1, X10.1; also elsewhere on the board
unnamed 81: Q6.3 (D), R52.1, X10.2; also elsewhere on the board
unnamed: R50.2, X8.A5 (CC1)
unnamed: R49.1, X8.B5 (CC2)
PWMB: X7.19; also elsewhere on the board
PWMG: X7.21; also elsewhere on the board
PWMR: X7.17; also elsewhere on the board
RS485_A: X13.3; also elsewhere on the board
RS485_B: X13.1; also elsewhere on the board
RS485_DE: X7.12; also elsewhere on the board
SCL0: Q5.2 (S), R2.1, X6.12 (SCL), X7.22; also elsewhere on the board
SDA0: Q6.2 (S), R1.1, X6.13 (SDA), X7.24; also elsewhere on the board
SPI0_MISO: X6.15 (MISO), X7.18; also elsewhere on the board
SPI0_MOSI: X6.16 (MOSI), X7.20; also elsewhere on the board
SW0: X7.4; also elsewhere on the board
SW1: X7.6; also elsewhere on the board
SW2: X7.8; also elsewhere on the board
SW3: X7.10; also elsewhere on the board
UART_RS485_RX: X6.22 (TX_1), X7.11; also elsewhere on the board
UART_RS485_TX: X6.21 (RX_1), X7.9; also elsewhere on the board
USB0_D+: D17.2, X8.A6 (DP1), X8.B6 (DP2); also elsewhere on the board
USB0_D-: D17.3, X8.A7 (DN1), X8.B7 (DN2); also elsewhere on the board
USB_UART0_TX: X6.20 (TX_0), X7.7; also elsewhere on the board
V_USB: D17.4, X8.A4 (VBUS), X8.A9 (VBUS); also elsewhere on the board
WS2812_DOUT: J2.2, X7.15; also elsewhere on the board
~General_Reset: X7.14; also elsewhere on the board

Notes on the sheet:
STEMMA https://learn.adafruit.com/introducing-adafruit-stemma-qt/technical-specs
USB-Common
Connectors - USB-Direct: USBC (USB) - RS485 Connector: ? (RS485 from Interface Chip) - USB-UART: USBC (USB from USB-Serial Convertor) - I2C: S4B-PH-SM4-K-TB(LF)(SN) + pin-header (I2C) - 40-Pin Header: PH-00650 (everything...)
